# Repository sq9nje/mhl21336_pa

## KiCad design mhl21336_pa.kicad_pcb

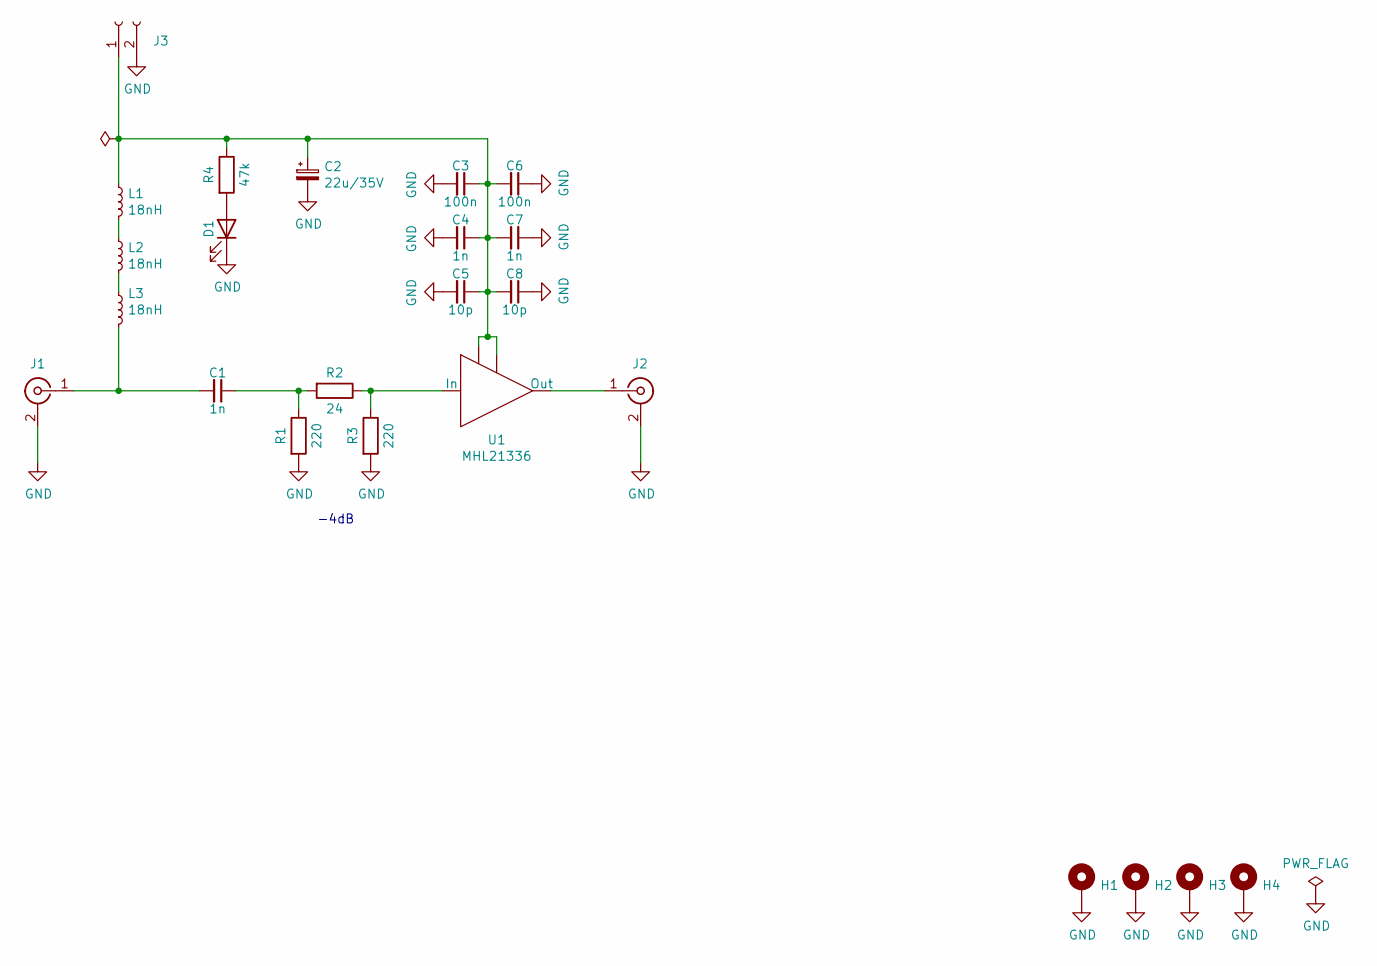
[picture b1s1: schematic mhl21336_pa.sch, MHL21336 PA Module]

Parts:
C1: 1n; C_0805_2012Metric_Pad1.18x1.45mm_HandSolder
C2: 22u/35V; CP_EIA-7343-31_Kemet-D_Pad2.25x2.55mm_HandSolder
C3, C6: 100n; C_0603_1608Metric_Pad1.08x0.95mm_HandSolder
C4, C7: 1n; C_0603_1608Metric_Pad1.08x0.95mm_HandSolder
C5, C8: 10p; C_0603_1608Metric_Pad1.08x0.95mm_HandSolder
D1: LED; LED_0805_2012Metric_Pad1.15x1.40mm_HandSolder
H1, H2, H3, H4: MountingHole_Pad; MountingHole_3.2mm_M3_DIN965_Pad
J1, J2: Conn_Coaxial; SMA_Samtec_SMA-J-P-X-ST-EM1_EdgeMount
J3: Conn_01x02_Female; JST_XH_B2B-XH-A_1x02_P2.50mm_Vertical
L1, L2, L3: 18nH; L_0603_1608Metric_Pad1.05x0.95mm_HandSolder
R1, R3: 220; R_0805_2012Metric_Pad1.20x1.40mm_HandSolder
R2: 24; R_0805_2012Metric_Pad1.20x1.40mm_HandSolder
R4: 47k; R_0805_2012Metric_Pad1.20x1.40mm_HandSolder
U1: MHL21336

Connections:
GND: C2.2, C3.2, C4.2, C5.2, C6.1, C7.1, C8.1, D1.1 (K), H1.1, H2.1, H3.1, H4.1, J1.2 (Ext), J2.2 (Ext), J3.2, R1.2, R3.2
unnamed: C1.1, R1.1, R2.2
unnamed: C1.2, J1.1 (In), L3.2
unnamed: C2.1, C3.1, C4.1, C5.1, C6.2, C7.2, C8.2, J3.1, L1.1, R4.1, U1.2 (Vdd1), U1.3 (Vdd2)
unnamed: D1.2 (A), R4.2
unnamed: J2.1 (In), U1.4 (Out)
unnamed: L1.2, L2.1
unnamed: L2.2, L3.1
unnamed: R2.1, R3.1, U1.1 (In)

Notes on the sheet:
-4dB

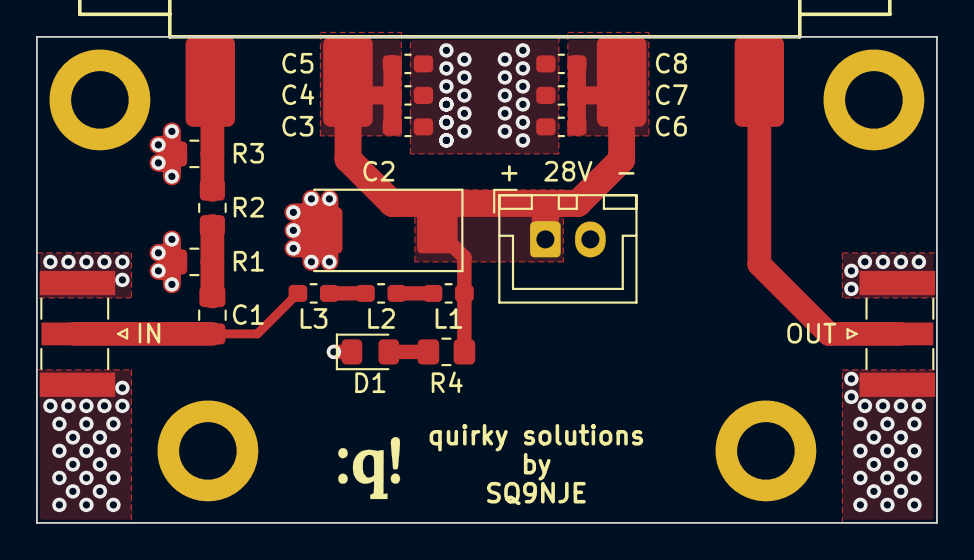
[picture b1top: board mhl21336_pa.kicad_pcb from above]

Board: 2 copper layers, 50.0 x 27.0 mm, 25 parts (0 on the bottom side), 9 nets.

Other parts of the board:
Ref**: Val**; qs_logo

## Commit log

2021-01-30 MHL21336 PA Module
2021-09-06 Interactive BOM
